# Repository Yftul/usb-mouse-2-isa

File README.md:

# usb-mouse-2-isa

**Проект / Project**
Подключение современной USB-мыши к старым ПК, ожидающим COM мышь.
Connect a modern USB mouse to an old PC expecting a COM mouse.

---

## Описание / Description

Проект `usb-mouse-2-isa` предназначен для реализации поддержки USB-мышей на ретро-компьютерах c ISA шиной.
The `usb-mouse-2-isa` project aims to provide USB mouse support on vintage computers with an ISA bus.

В основе — микроконтроллер и программируемая логика, которая:
At the core are a microcontroller and programmable logic that:

- принимает сигналы от USB-мыши / receive data from a USB mouse;
- преобразует в эмуляцию COM портовой мыши на ISA шине / converts into an emulation of a serial mouse on ISA bus.
- обеспечивает базовую функциональность: движение, нажатие кнопок, прокрутку / provide basic functionality: movement, button clicks, and wheel scrolling.

---

## Общие сведения / General info
Устройство устанавливается в ISA слот. Мышь подключается в USB разъём. При сбросе компьютера, включении и отключении мыши мигает светодиод активности VD1. Также он мигает, если работает драйвер выши и мышь проявляет какую-либо активность.
Перемычками COM SEL J4 можно выбрать COM порт COM1-COM4. При необходимости выбрать нестандартное прерывание, нужно установить перемычку IRQX J5 и выбрать необходимое прерывание IRQ2,5,6,7 установкой перемычки J1. Например:
оставив J4 1-2 3-4 и J5 5-6 без перемычек(open), устройство будет настроена на работу в качестве порта COM1 со стандартными port и IRQ 0x3F8/IRQ3. Если же установить все три перемычки, устройство будет откликаться на стандартный адрес COM4 0x2E8, но из-за установленного IRQX использовать один их IRQ2,5,6,7, выбранный перемычкой J1.
Все комбинации перемычек подписаны на плате.

Кроме того, можно выбрать поддержку колесика мыши, установив перемычку wheel J4 5-6. И уменьшить частоту передачи данных мыши по порту, установив перемычки Rate, где открытым(open) перемычкам соответсвует скорость передачи по умолчанию, устанавливая перемычки, замедляем скорость передачи до 4х раз.

--/

The device is installed into an ISA slot. The mouse is connected to the USB port. When the computer is reset, powered on, or when the mouse is plugged  or unplugged, the activity LED VD1 blinks. It also blinks when the mouse driver is running and the mouse generates any activity.

The COM SEL J4 jumpers allow selecting the COM port number (COM1–COM4). If a non‑standard interrupt is required, you must enable the IRQX jumper J5 and select the desired interrupt (IRQ2, 5, 6, or 7) using jumper J1. Examples:

 - if J4 1–2 and 3–4 are closed, and J5 5–6 is open, the device will be configured as COM1 with the standard port and IRQ (0x3F8 / IRQ3).
 - if all three jumpers are closed, the device will be at the standard COM4 address 0x2E8, but because IRQX is enabled, it will use one of IRQ2, 5, 6, or 7 selected by the jumper J1.

All possible jumpers combinations are written on the PCB.

Additionally, mouse wheel support can be enabled by closing the “wheel” jumper J4 5–6.  
You can also reduce the mouse data rate by configuring the Rate jumpers: the open (default) position corresponds to the normal data rate, and installing the jumpers reduces the rate by up to 4×.

## Структура репозитория / Repository structure

- `MCU/` — исходники микроконтроллера (C/ASM). / microcontroller firmware (C/ASM).
- `CPLD/` — исходники CPLD (VHDL). / CPLD logic design (VHDL).
- `SCHEME/` — схемы подключения, разводка. / schematics, wiring.
- `BIN/` — собранные прошивки. / compiled firmware.
- `README.md` — этот файл. / this README.
- `LICENSE` — лицензия проекта (GPL-3.0). / license file (GPL-3.0).

---

## Требования железа / Hardware requirements

- USB HID-мышь. / USB HID mouse.
- ПК с ISA-шиной и свободными ресурсами для подключения эмулируемого COM порта. / PC with ISA bus and enouth free resources to attach emulated COM port.
- Стандартный драйвер COM мыши / Standard serial mouse driver.

---

## Требования ПО / Software requirements

```bash
# 1. Сборка прошивки микроконтроллера / MCU firmware build
MCU: make clean && make

# 2. Для прошивки используется утилита WCHISPTool и кабель "USB-A - USB-A" / To flash MCU use WCHISPTool and cable "USB-A - USB-A"

# 3. Cинтез и прошивка CPLD / FPGA sinthesis and flash
Quartus 13 or earlier  + Altera byte blaster

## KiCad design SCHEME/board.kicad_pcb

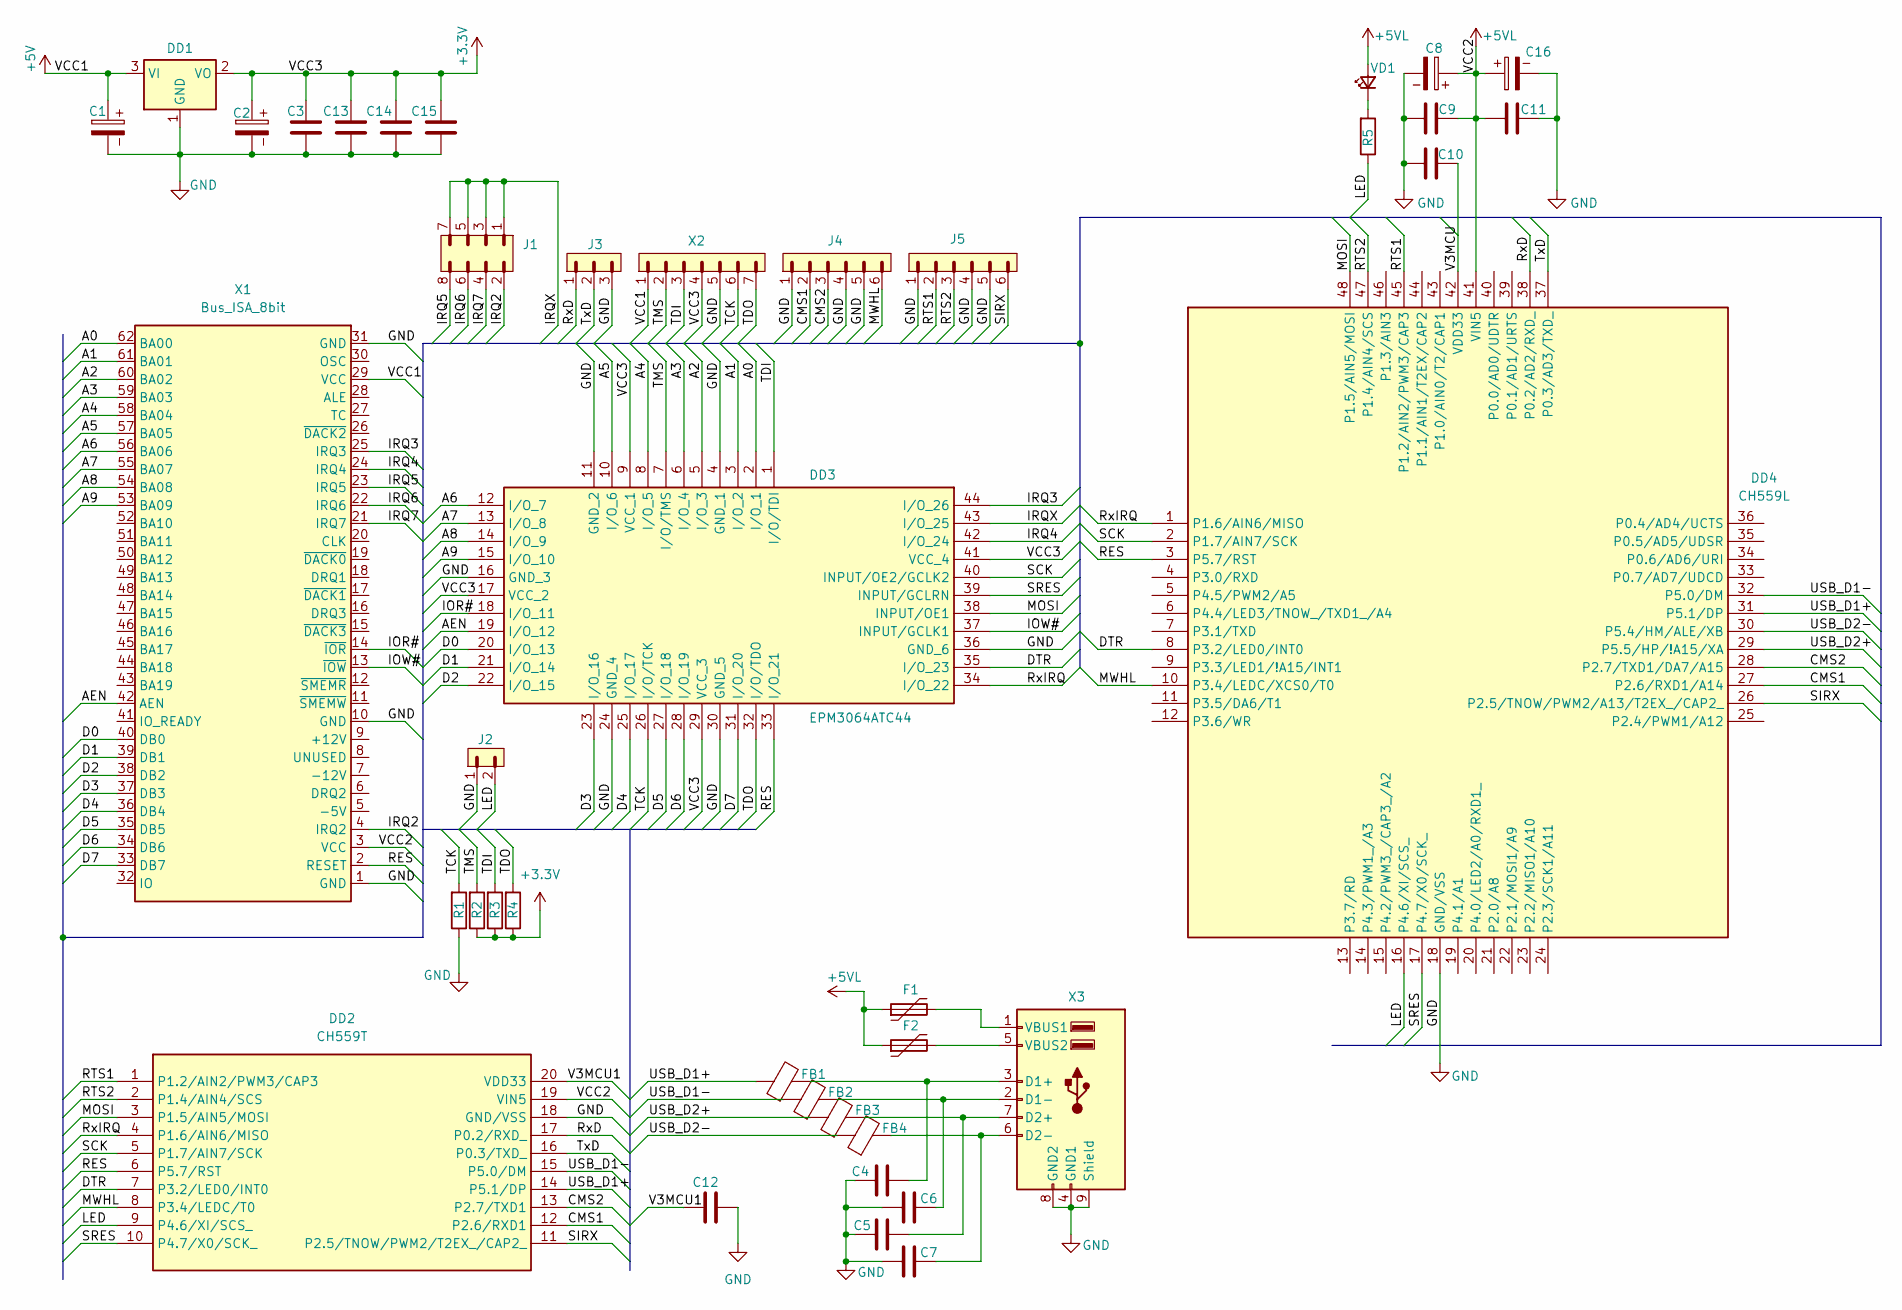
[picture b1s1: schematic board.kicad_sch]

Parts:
C1, C2, C16: 10u; CP_Radial_D5.0mm_P2.00mm
C3, C9, C10, C11, C12, C13, C14, C15: 0.1; C_0805_2012Metric
C4, C5, C6, C7: 220p; C_0805_2012Metric
C8: 33u; CP_Radial_D5.0mm_P2.00mm
DD1: LM1117DT-3.3; TO-252-3_TabPin2
DD2: CH559T; SSOP-20_5.3x7.2mm_P0.65mm; Manufacturer_Part_Number CH559L
DD3: EPM3064ATC44; TQFP-44_10x10mm_P0.8mm; Manufacturer_Part_Number EPM3032ATC44-4N; Mouser Part Number 989-EPM3032ATC44-4N
DD4: CH559L; LQFP-48_7x7mm_P0.5mm; Manufacturer_Part_Number CH559L
F1: Polyfuse_3A_15V; Fuse_1812_4532Metric; Part Number miniSMDC150F/24; JLCPCB ID C207070
F2: 500mA; Fuse_1812_4532Metric; Part Number miniSMDC150F/24; JLCPCB ID C207070
FB1, FB2, FB3, FB4: L_1206_3216Metric_Pad1.22x1.90mm_HandSolder
J1: PINHD_2x4_Male; PinHeader_2x04_P2.54mm_Vertical
J2: PINHD_1x2_Male; PinHeader_1x02_P2.54mm_Vertical
J3: PINHD_1x3_Male; PinHeader_1x03_P2.54mm_Vertical
J4, J5: PINHD_1x6_Male; PinHeader_1x06_P2.54mm_Vertical
R1, R2, R3, R4: 4.7k; R_0805_2012Metric
R5: 560; R_0805_2012Metric
VD1: LED; LED_D3.0mm_Horizontal_O1.27mm_Z2.0mm
X1: Bus_ISA_8bit; BUS_XT
X2: PINHD_1x7_Male; PinHeader_1x07_P2.54mm_Vertical
X3: USB_A_Stacked; USB_A_CUI_UJ2-ADH-TH_Horizontal_Stacked

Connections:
+3.3V: C2.1, C3.1, C13.1, C14.1, C15.1, DD1.2 (VO), DD3.9 (VCC_1), DD3.17 (VCC_2), DD3.29 (VCC_3), DD3.41 (VCC_4), R2.2, R3.2, R4.2, X2.4
+5V: C1.1, DD1.3 (VI), X1.29 (VCC), X2.1
+5VL: C8.1, C9.2, C11.1, C16.1, DD2.19 (VIN5), DD4.41 (VIN5), F1.1, F2.1, VD1.2 (A), X1.3 (VCC)
/A0: DD3.2 (I/O_1), X1.62 (BA00)
/A1: DD3.3 (I/O_2), X1.61 (BA01)
/A2: DD3.5 (I/O_3), X1.60 (BA02)
/A3: DD3.6 (I/O_4), X1.59 (BA03)
/A4: DD3.8 (I/O_5), X1.58 (BA04)
/A5: DD3.10 (I/O_6), X1.57 (BA05)
/A6: DD3.12 (I/O_7), X1.56 (BA06)
/A7: DD3.13 (I/O_8), X1.55 (BA07)
/A8: DD3.14 (I/O_9), X1.54 (BA08)
/A9: DD3.15 (I/O_10), X1.53 (BA09)
/AEN: DD3.19 (I/O_12), X1.42 (AEN)
/CMS1: DD2.12 (P2.6/RXD1), DD4.27 (P2.6/RXD1/A14), J4.2
/CMS2: DD2.13 (P2.7/TXD1), DD4.28 (P2.7/TXD1/DA7/A15), J4.3
/D0: DD3.20 (I/O_13), X1.40 (DB0)
/D1: DD3.21 (I/O_14), X1.39 (DB1)
/D2: DD3.22 (I/O_15), X1.38 (DB2)
/D3: DD3.23 (I/O_16), X1.37 (DB3)
/D4: DD3.25 (I/O_17), X1.36 (DB4)
/D5: DD3.27 (I/O_18), X1.35 (DB5)
/D6: DD3.28 (I/O_19), X1.34 (DB6)
/D7: DD3.31 (I/O_20), X1.33 (DB7)
/DTR: DD2.7 (P3.2/LED0/INT0), DD3.35 (I/O_23), DD4.8 (P3.2/LED0/INT0)
/IOR#: DD3.18 (I/O_11), X1.14 (~IOR)
/IOW#: DD3.37 (INPUT/GCLK1), X1.13 (~IOW)
/IRQ2: J1.2, X1.4 (IRQ2)
/IRQ3: DD3.44 (I/O_26), X1.25 (IRQ3)
/IRQ4: DD3.42 (I/O_24), X1.24 (IRQ4)
/IRQ5: J1.8, X1.23 (IRQ5)
/IRQ6: J1.6, X1.22 (IRQ6)
/IRQ7: J1.4, X1.21 (IRQ7)
/IRQX: DD3.43 (I/O_25), J1.1, J1.3, J1.5, J1.7
/LED: DD2.9 (P4.6/XI/SCS_), DD4.16 (P4.6/XI/SCS_), J2.2, R5.2
/MOSI: DD2.3 (P1.5/AIN5/MOSI), DD3.38 (INPUT/OE1), DD4.48 (P1.5/AIN5/MOSI)
/MWHL: DD2.8 (P3.4/LEDC/T0), DD4.10 (P3.4/LEDC/XCS0/T0), J4.6
/RES: DD2.6 (P5.7/RST), DD3.33 (I/O_21), DD4.3 (P5.7/RST), X1.2 (RESET)
/RTS1: DD2.1 (P1.2/AIN2/PWM3/CAP3), DD4.45 (P1.2/AIN2/PWM3/CAP3), J5.2
/RTS2: DD2.2 (P1.4/AIN4/SCS), DD4.47 (P1.4/AIN4/SCS), J5.3
/RxD: DD2.17 (P0.2/RXD_), DD4.38 (P0.2/AD2/RXD_), J3.1
/RxIRQ: DD2.4 (P1.6/AIN6/MISO), DD3.34 (I/O_22), DD4.1 (P1.6/AIN6/MISO)
/SCK: DD2.5 (P1.7/AIN7/SCK), DD3.40 (INPUT/OE2/GCLK2), DD4.2 (P1.7/AIN7/SCK)
/SIRX: DD2.11 (P2.5/TNOW/PWM2/T2EX_/CAP2_), DD4.26 (P2.5/TNOW/PWM2/A13/T2EX_/CAP2_), J5.6
/SRES: DD2.10 (P4.7/X0/SCK_), DD3.39 (INPUT/GCLRN), DD4.17 (P4.7/X0/SCK_)
/TCK: DD3.26 (I/O/TCK), R1.1, X2.6
/TDI: DD3.1 (I/O/TDI), R3.1, X2.3
/TDO: DD3.32 (I/O/TDO), R4.1, X2.7
/TMS: DD3.7 (I/O/TMS), R2.1, X2.2
/TxD: DD2.16 (P0.3/TXD_), DD4.37 (P0.3/AD3/TXD_), J3.2
/USB_D1+: DD2.14 (P5.1/DP), DD4.31 (P5.1/DP), FB1.1
/USB_D1-: DD2.15 (P5.0/DM), DD4.32 (P5.0/DM), FB2.1
/USB_D2+: DD4.29 (P5.5/HP/!A15/XA), FB3.1
/USB_D2-: DD4.30 (P5.4/HM/ALE/XB), FB4.1
/V3MCU: C10.2, DD4.42 (VDD33)
/V3MCU1: C12.1, DD2.20 (VDD33)
GND: C1.2, C2.2, C3.2, C4.1, C5.1, C6.1, C7.1, C8.2, C9.1, C10.1, C11.2, C12.2, C13.2, C14.2, C15.2, C16.2, DD1.1 (GND), DD2.18 (GND/VSS), DD3.4 (GND_1), DD3.11 (GND_2), DD3.16 (GND_3), DD3.24 (GND_4), DD3.30 (GND_5), DD3.36 (GND_6), DD4.18 (GND/VSS), J2.1, J3.3, J4.1, J4.4, J4.5, J5.1, J5.4, J5.5, R1.2, X1.1 (GND), X1.10 (GND), X1.31 (GND), X2.5, X3.4 (GND1), X3.8 (GND2), X3.9 (Shield)
unnamed: R5.1, VD1.1 (K)
unnamed: C4.2, FB1.2, X3.3 (D1+)
unnamed: C6.2, FB2.2, X3.2 (D1-)
unnamed: C5.2, FB3.2, X3.7 (D2+)
unnamed: C7.2, FB4.2, X3.6 (D2-)
unnamed: F1.2, X3.1 (VBUS1)
unnamed: F2.2, X3.5 (VBUS2)

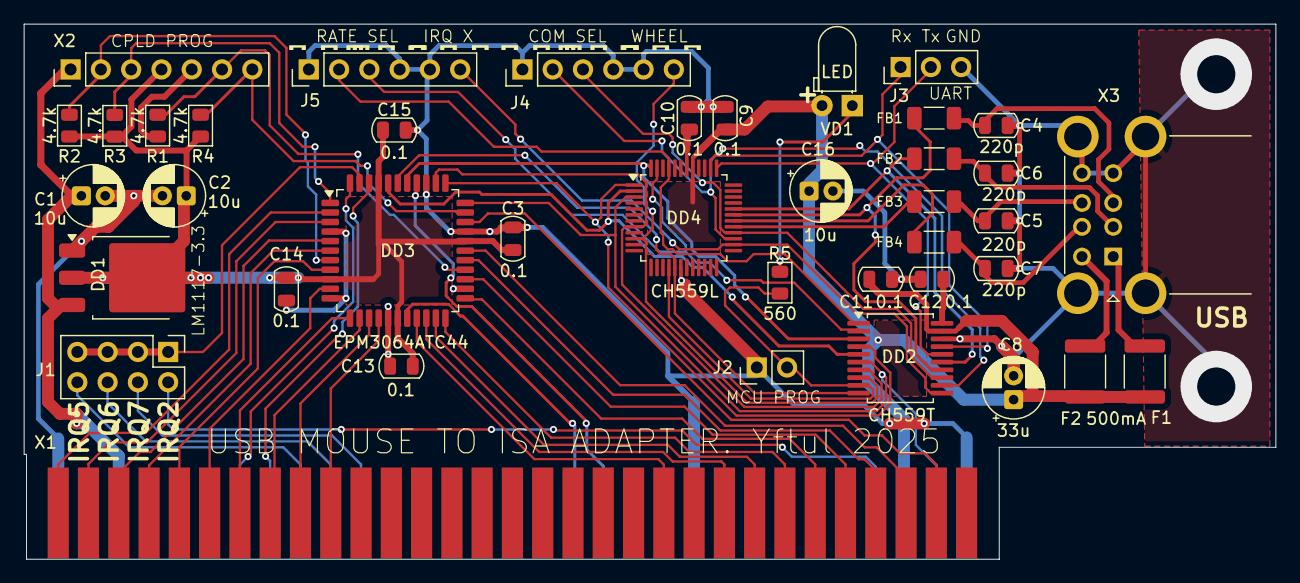
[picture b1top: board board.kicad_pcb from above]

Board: 2 copper layers, 105.0 x 44.9 mm, 40 parts (0 on the bottom side), 64 nets.

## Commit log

2025-12-02 Workable version, knows issues: 1. Board not completely fit to isa slot, requires filing; 2. Too small too small seating areas for beads; 3. Looks, lines from CH559T are too long, workable only with 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
2025-12-02 Removed temporary build directory
2025-12-03 Added nop to fix the issues with long wiring to ch559t; Updated readme.
2025-12-03 Removed obsolete files
2025-12-04 Rate issue fix
2025-12-04 Reverted wheel sign
2025-12-04 Fixed configuration issue
2026-01-09 Updated board: 1. Reduced ISA slot; 2. Changed beads from 0805 to 1206; 3. General trace improvements.
2026-01-09 Added fab files
2026-02-20 Fix compatibility issues of complex HID devices
2026-03-01 Added latest binary
2026-03-12 fix C23
2026-03-22 Added BOM
